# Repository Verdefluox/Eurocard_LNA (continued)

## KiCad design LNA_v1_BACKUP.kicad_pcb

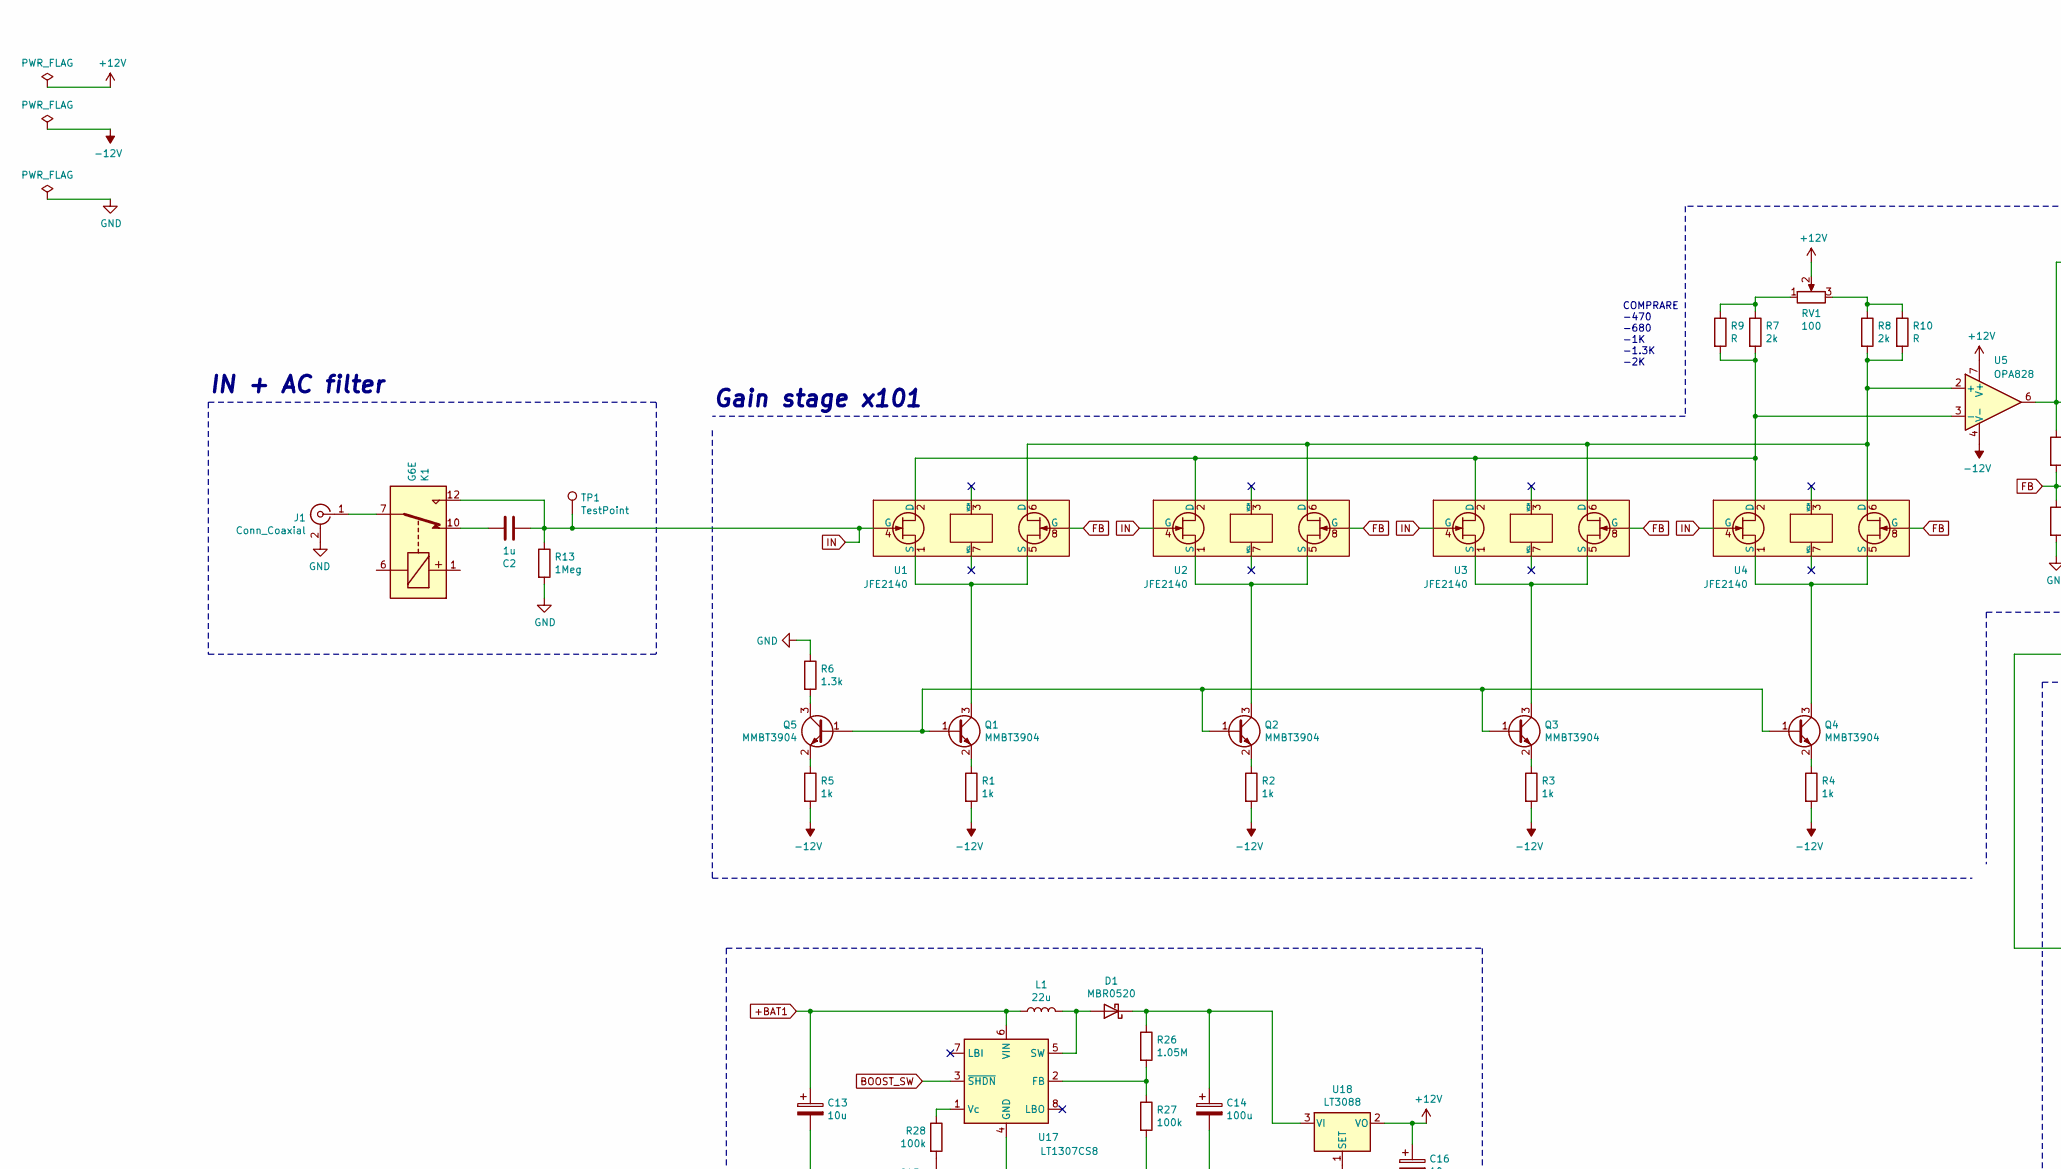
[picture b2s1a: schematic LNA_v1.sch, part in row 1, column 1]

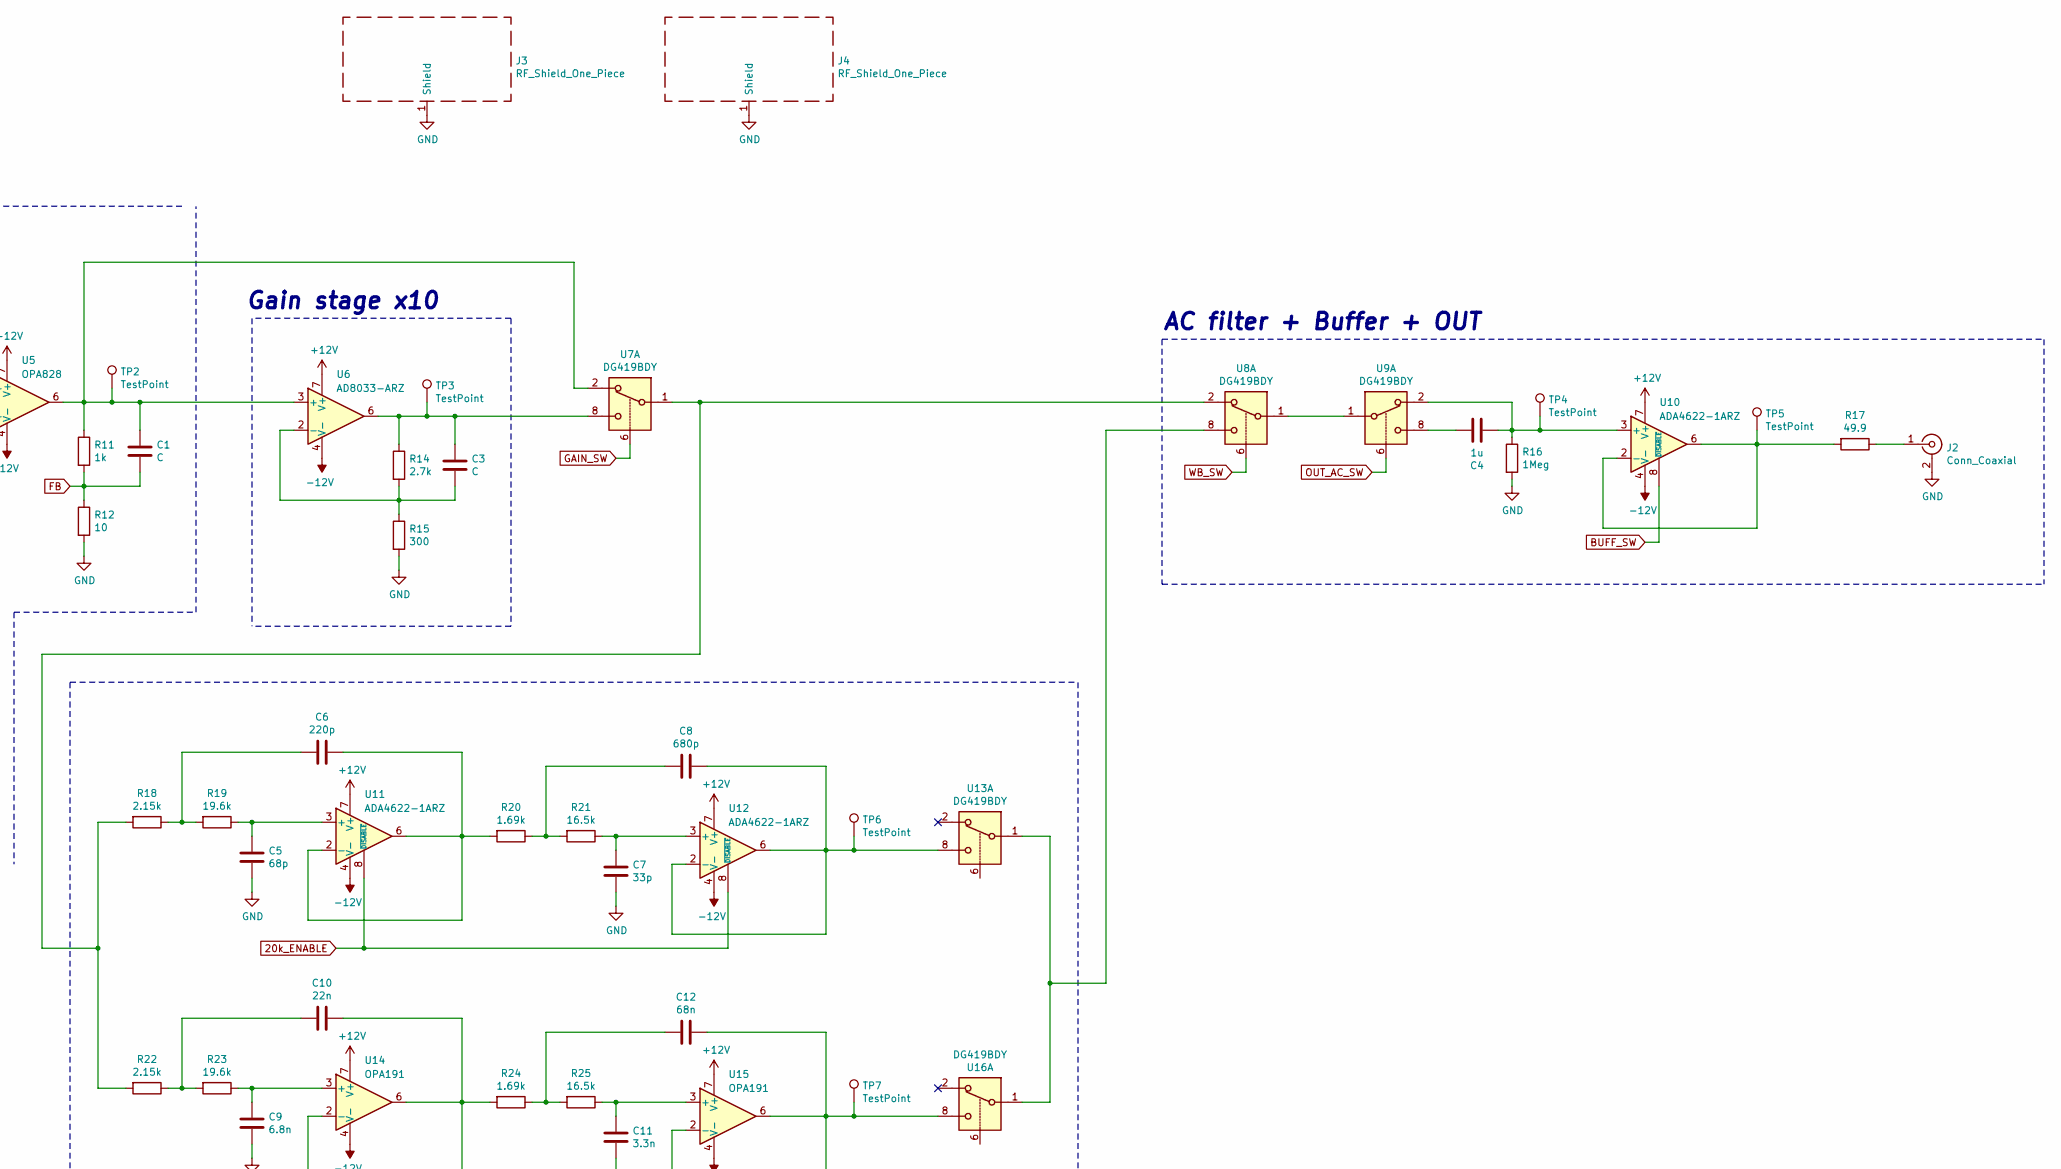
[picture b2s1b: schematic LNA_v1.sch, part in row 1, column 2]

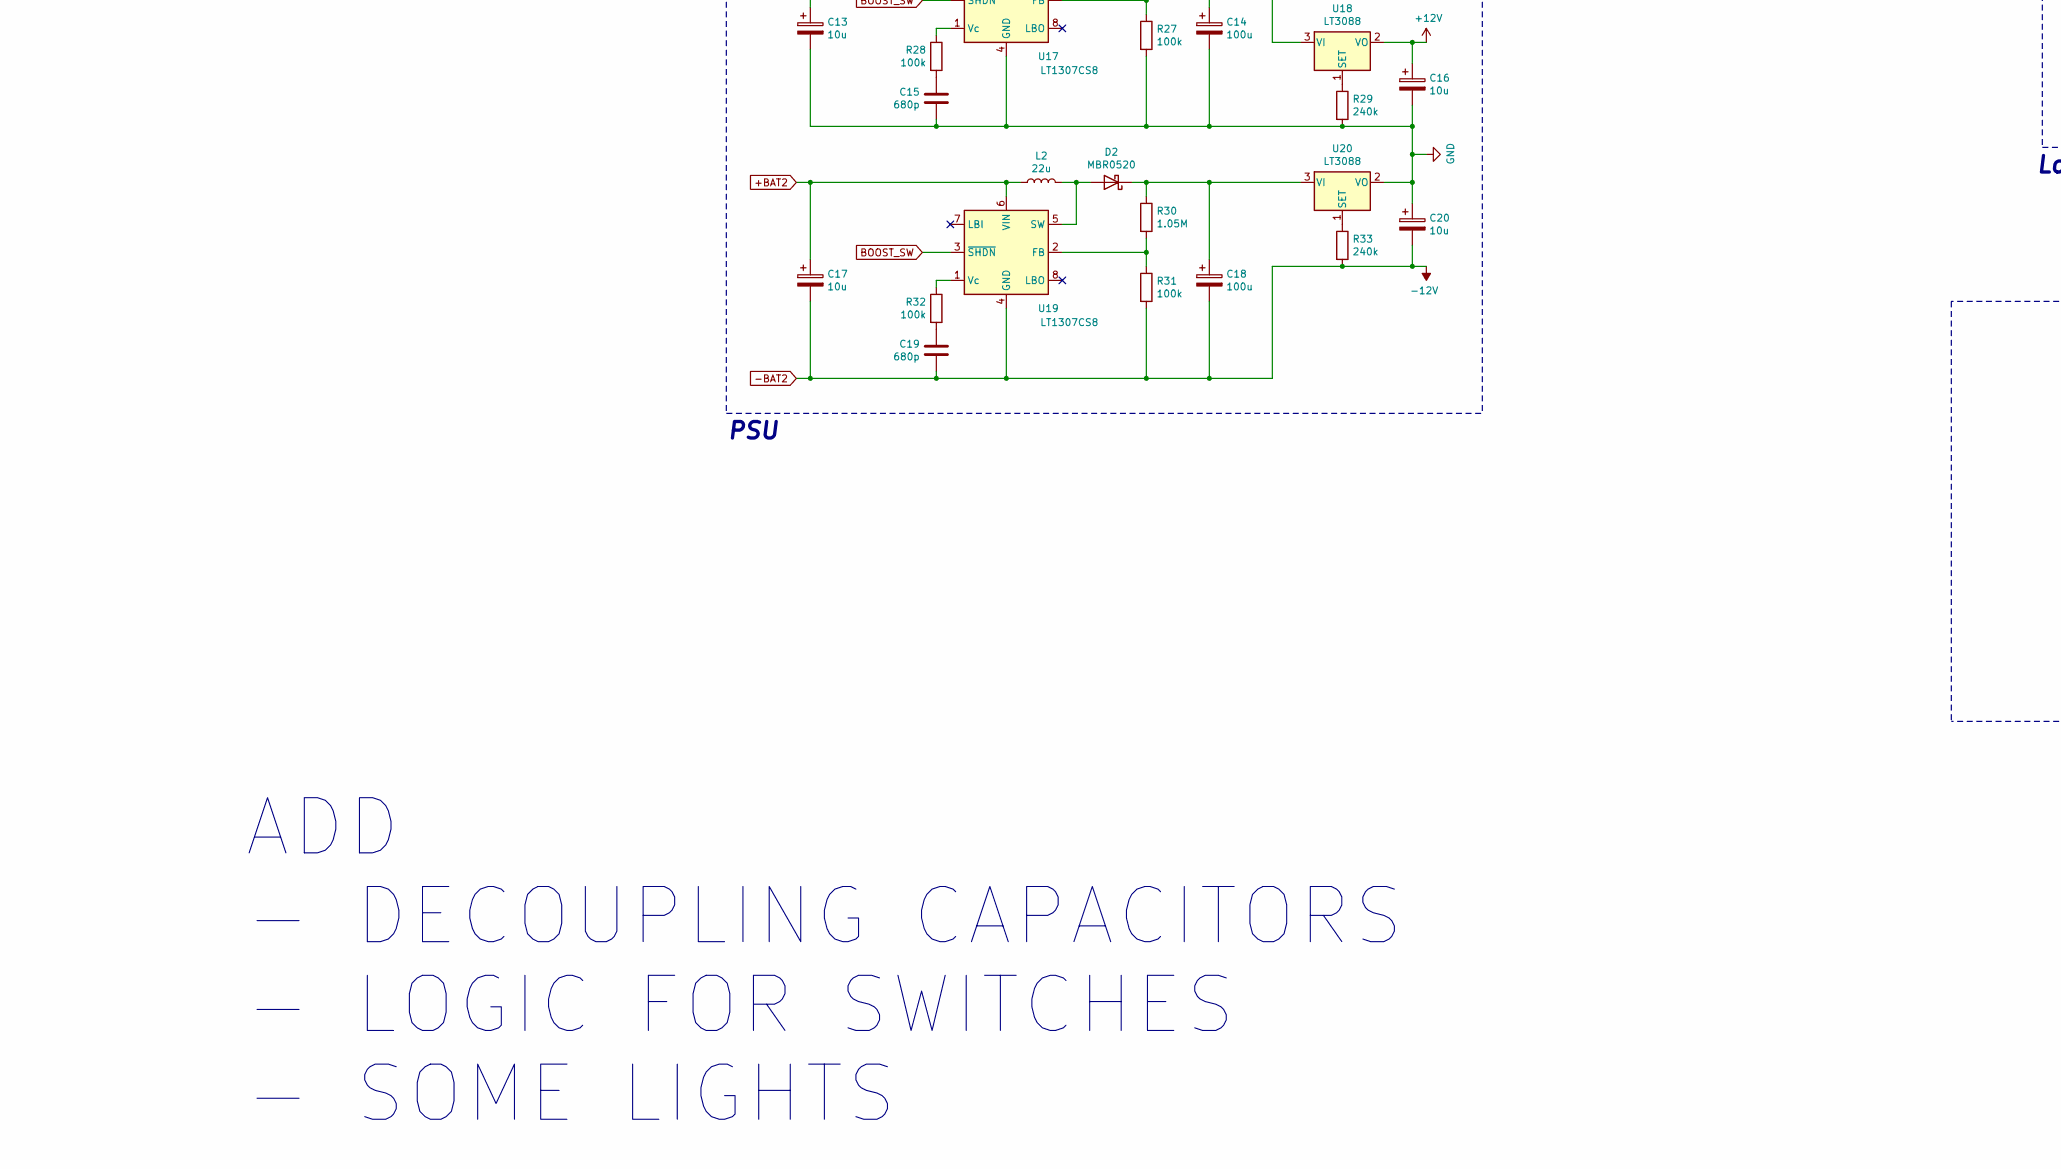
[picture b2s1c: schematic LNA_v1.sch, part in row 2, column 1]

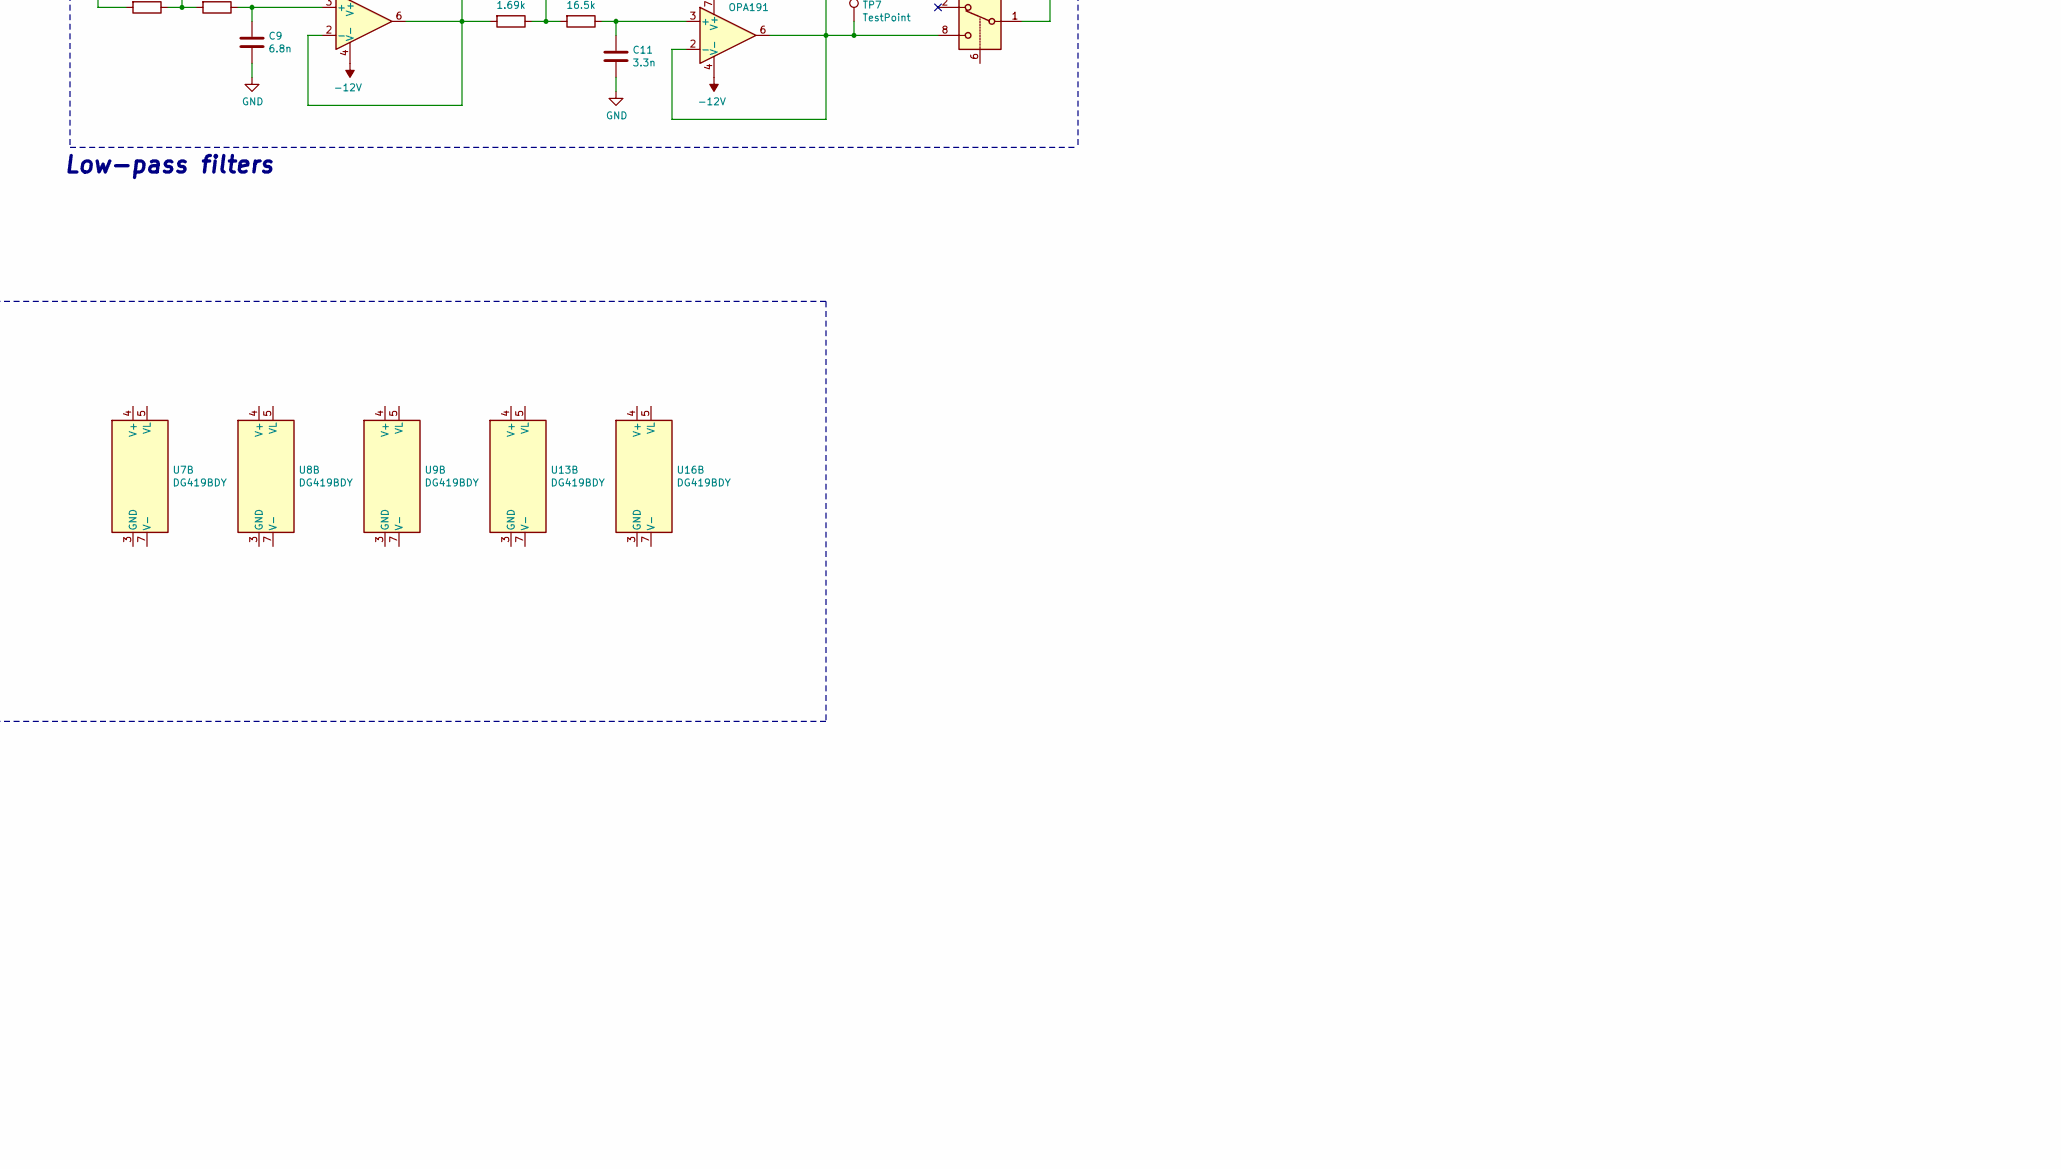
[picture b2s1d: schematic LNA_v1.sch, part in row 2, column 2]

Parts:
C1, C3: C; C_1206_3216Metric_Pad1.33x1.80mm_HandSolder
C2, C4: 1u; C_Rect_L16.5mm_W7.3mm_P15.00mm_MKT
C5: 68p; C_1206_3216Metric_Pad1.33x1.80mm_HandSolder
C6: 220p; C_1206_3216Metric_Pad1.33x1.80mm_HandSolder
C7: 33p; C_1206_3216Metric_Pad1.33x1.80mm_HandSolder
C8, C15, C19: 680p; C_1206_3216Metric_Pad1.33x1.80mm_HandSolder
C9: 6.8n; C_1206_3216Metric_Pad1.33x1.80mm_HandSolder
C10: 22n; C_1206_3216Metric_Pad1.33x1.80mm_HandSolder
C11: 3.3n; C_1206_3216Metric_Pad1.33x1.80mm_HandSolder
C12: 68n; C_1206_3216Metric_Pad1.33x1.80mm_HandSolder
C13, C16, C17, C20: 10u; CP_Elec_6.3x5.8
C14, C18: 100u; CP_Elec_6.3x7.7
D1, D2: MBR0520; D_SOD-123
J1, J2: Conn_Coaxial; BNC_Amphenol_B6252HB-NPP3G-50_Horizontal
J3, J4: RF_Shield_One_Piece; Wuerth_36103255_25x25mm
K1: G6E; Relay_SPDT_Omron_G6E
L1, L2: 22u; L_Bourns-SRN1060
Q1, Q2, Q3, Q4, Q5: MMBT3904; SOT-23W
R1, R2, R3, R4, R5, R11: 1k; R_1206_3216Metric_Pad1.30x1.75mm_HandSolder
R6: 1.3k; R_1206_3216Metric_Pad1.30x1.75mm_HandSolder
R7, R8: 2k; R_1206_3216Metric_Pad1.30x1.75mm_HandSolder
R9, R10: R; R_1206_3216Metric_Pad1.30x1.75mm_HandSolder
R12: 10; R_1206_3216Metric_Pad1.30x1.75mm_HandSolder
R13, R16: 1Meg; R_1206_3216Metric_Pad1.30x1.75mm_HandSolder
R14: 2.7k; R_1206_3216Metric_Pad1.30x1.75mm_HandSolder
R15: 300; R_1206_3216Metric_Pad1.30x1.75mm_HandSolder
R17: 49.9; R_1206_3216Metric_Pad1.30x1.75mm_HandSolder
R18, R22: 2.15k; R_1206_3216Metric_Pad1.30x1.75mm_HandSolder
R19, R23: 19.6k; R_1206_3216Metric_Pad1.30x1.75mm_HandSolder
R20, R24: 1.69k; R_1206_3216Metric_Pad1.30x1.75mm_HandSolder
R21, R25: 16.5k; R_1206_3216Metric_Pad1.30x1.75mm_HandSolder
R26, R30: 1.05M; R_1206_3216Metric_Pad1.30x1.75mm_HandSolder
R27, R28, R31, R32: 100k; R_1206_3216Metric_Pad1.30x1.75mm_HandSolder
R29, R33: 240k; R_1206_3216Metric_Pad1.30x1.75mm_HandSolder
RV1: 100; Potentiometer_Bourns_3296W_Vertical
TP1: TestPoint; TestPoint_Pad_D1.5mm
TP2, TP3, TP4, TP5, TP6, TP7: TestPoint; TestPoint_THTPad_D2.5mm_Drill1.2mm
U1, U2, U3, U4: JFE2140; SOIC-8_3.9x4.9mm_P1.27mm
U5: OPA828; SOIC-8_3.9x4.9mm_P1.27mm
U6: AD8033-ARZ; SOIC-8_3.9x4.9mm_P1.27mm
U7, U8, U9, U13, U16: DG419BDY; SOIC-8_3.9x4.9mm_P1.27mm
U10, U11, U12: ADA4622-1ARZ; SOIC-8_3.9x4.9mm_P1.27mm
U14, U15: OPA191; SOIC-8_3.9x4.9mm_P1.27mm
U17, U19: LT1307CS8; SOIC-8_3.9x4.9mm_P1.27mm
U18, U20: LT3088; SOT-223

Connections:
20k_ENABLE: U11.8 (~DISABLE), U12.8 (~DISABLE)
+12V: C16.1, RV1.2, U5.7 (V+), U6.7 (V+), U10.7 (V+), U11.7 (V+), U12.7 (V+), U14.7 (V+), U15.7 (V+), U18.2 (VO)
+BAT1: C13.1, L1.1, U17.6 (VIN)
+BAT2: C17.1, L2.1, U19.6 (VIN)
-BAT2: C17.2, C18.2, C19.2, C20.2, R1.2, R2.2, R3.2, R4.2, R5.2, R31.2, R33.2, U5.4 (V-), U6.4 (V-), U10.4 (V-), U11.4 (V-), U12.4 (V-), U14.4 (V-), U15.4 (V-), U19.4 (GND)
BOOST_SW: U17.3 (~SHDN), U19.3 (~SHDN)
BUFF_SW: U10.8 (~DISABLE)
FB: C1.2, R11.2, R12.1, U1.8 (G), U2.8 (G), U3.8 (G), U4.8 (G)
GAIN_SW: U7.6
GND: C5.1, C7.1, C9.1, C11.1, C13.2, C14.2, C15.2, C16.2, C20.1, J1.2 (Ext), J2.2 (Ext), J3.1, J4.1, R6.1, R12.2, R13.2, R15.2, R16.2, R27.2, R29.2, U17.4 (GND), U20.2 (VO)
IN: C2.1, K1.12, R13.1, TP1.1, U1.4 (G), U2.4 (G), U3.4 (G), U4.4 (G)
unnamed: C1.1, R11.1, TP2.1, U5.6, U6.3 (+), U7.2
unnamed: C2.2, K1.10
unnamed: C3.1, R14.1, TP3.1, U6.6, U7.8
unnamed: C3.2, R14.2, R15.1, U6.2 (-)
unnamed: C4.1, R16.1, TP4.1, U9.2, U10.3 (+)
unnamed: C4.2, U9.8
unnamed: C5.2, R19.1, U11.3 (+)
unnamed: C6.1, R20.2, U11.2 (-), U11.6
unnamed: C6.2, R18.1, R19.2
unnamed: C7.2, R21.1, U12.3 (+)
unnamed: C8.1, TP6.1, U12.2 (-), U12.6, U13.8
unnamed: C8.2, R20.1, R21.2
unnamed: C9.2, R23.1, U14.3 (+)
unnamed: C10.1, R24.2, U14.2 (-), U14.6
unnamed: C10.2, R22.1, R23.2
unnamed: C11.2, R25.1, U15.3 (+)
unnamed: C12.1, TP7.1, U15.2 (-), U15.6, U16.8
unnamed: C12.2, R24.1, R25.2
unnamed: C14.1, D1.1 (K), R26.1, U18.3 (VI)
unnamed: C15.1, R28.2
unnamed: C18.1, D2.1 (K), R30.1, U20.3 (VI)
unnamed: C19.1, R32.2
unnamed: D1.2 (A), L1.2, U17.5 (SW)
unnamed: D2.2 (A), L2.2, U19.5 (SW)
unnamed: J1.1 (In), K1.7
unnamed: J2.1 (In), R17.1
unnamed: Q1.1 (B), Q2.1 (B), Q3.1 (B), Q4.1 (B), Q5.1 (B)
unnamed: Q1.2 (E), R1.1
unnamed: Q1.3 (C), U1.1 (S), U1.5 (S)
unnamed: Q2.2 (E), R2.1
unnamed: Q2.3 (C), U2.1 (S), U2.5 (S)
unnamed: Q3.2 (E), R3.1
unnamed: Q3.3 (C), U3.1 (S), U3.5 (S)
unnamed: Q4.2 (E), R4.1
unnamed: Q4.3 (C), U4.1 (S), U4.5 (S)
unnamed: Q5.2 (E), R5.1
unnamed: Q5.3 (C), R6.2
unnamed: R7.1, R9.1, RV1.1
unnamed: R7.2, R9.2, U1.2 (D), U2.2 (D), U3.2 (D), U4.2 (D), U5.3 (-)
unnamed: R8.1, R10.1, RV1.3
unnamed: R8.2, R10.2, U1.6 (D), U2.6 (D), U3.6 (D), U4.6 (D), U5.2 (+)
unnamed: R17.2, TP5.1, U10.2 (-), U10.6
unnamed: R18.2, R22.2, U7.1, U8.2
unnamed: R26.2, R27.1, U17.2 (FB)
unnamed: R28.1, U17.1 (Vc)
unnamed: R29.1, U18.1 (SET)
unnamed: R30.2, R31.1, U19.2 (FB)
unnamed: R32.1, U19.1 (Vc)
unnamed: R33.1, U20.1 (SET)
unnamed: U8.1, U9.1
unnamed: U8.8, U13.1, U16.1
OUT_AC_SW: U9.6
WB_SW: U8.6

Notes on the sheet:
AC filter + Buffer + OUT
COMPRARE -470 -680 -1K -1.3K -2K
PSU
Gain stage x101
Low-pass filters
Gain stage x10
IN + AC filter
ADD - DECOUPLING CAPACITORS - LOGIC FOR SWITCHES - SOME LIGHTS

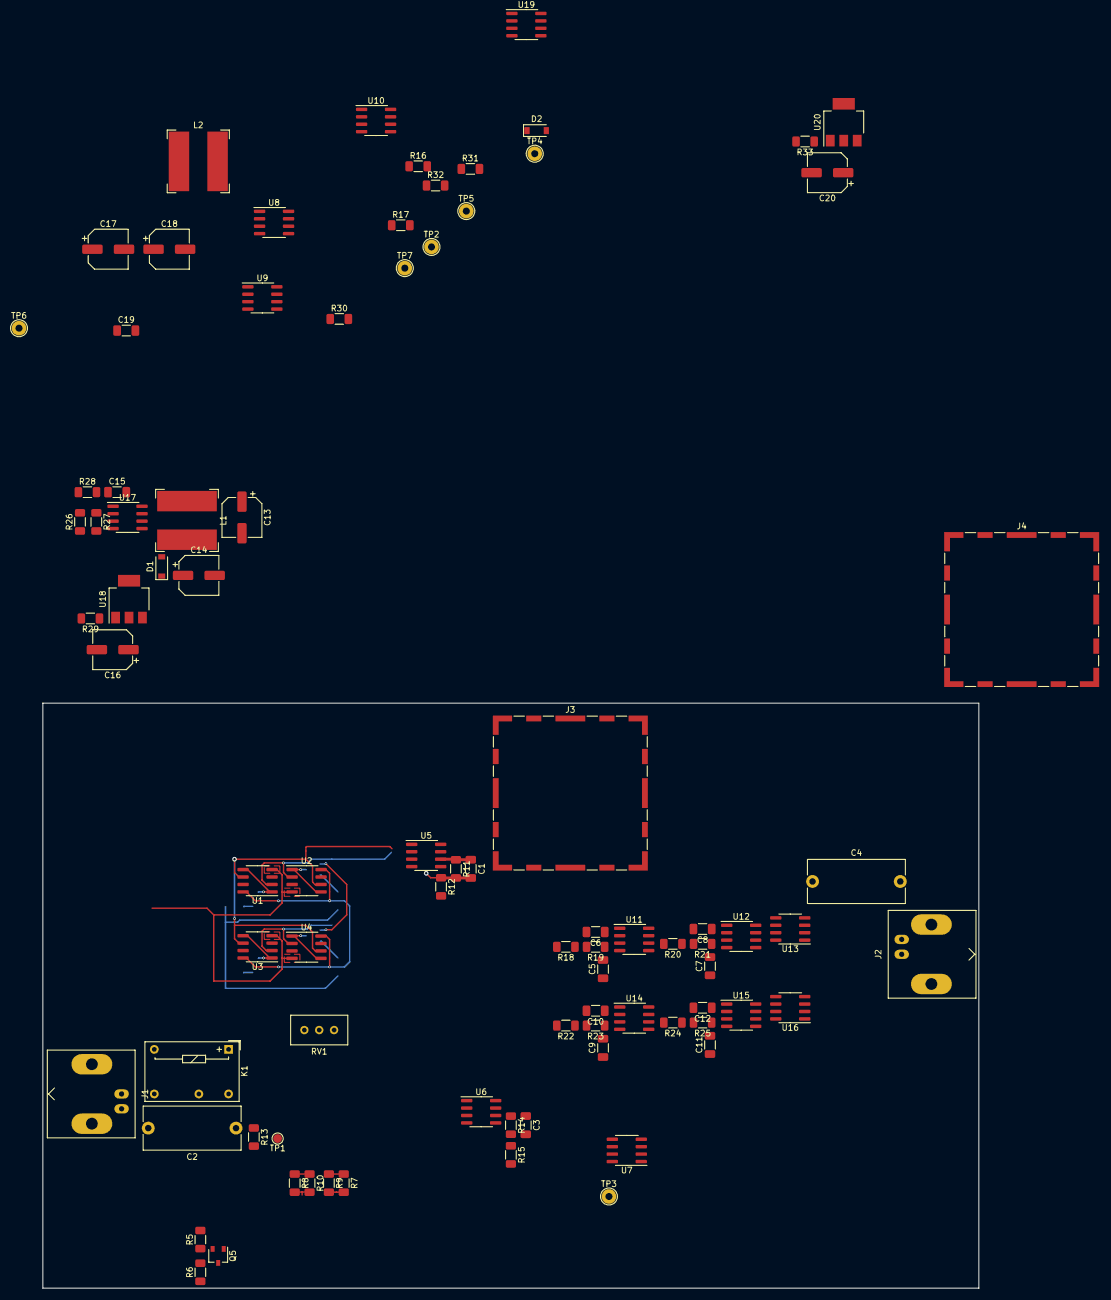
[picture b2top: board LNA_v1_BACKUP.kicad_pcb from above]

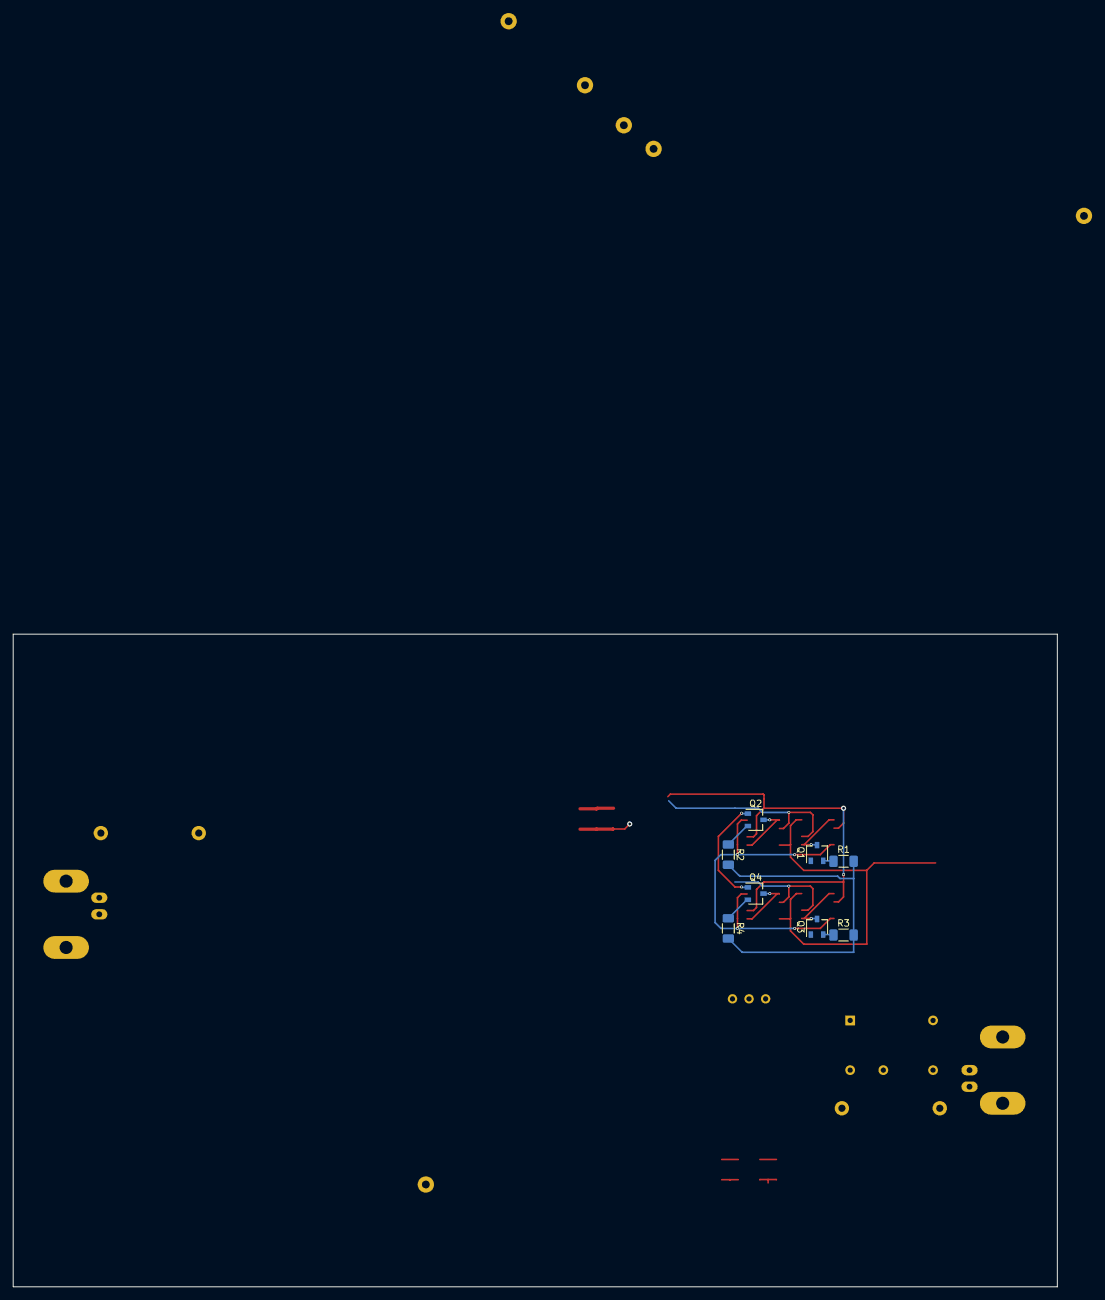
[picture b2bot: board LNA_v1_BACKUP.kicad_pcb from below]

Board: 2 copper layers, 160.0 x 100.0 mm, 95 parts (8 on the bottom side), 60 nets.

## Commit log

2025-04-06 Update README.md
    Description of the project
2025-08-28 Added main files: v1; rev. 1
